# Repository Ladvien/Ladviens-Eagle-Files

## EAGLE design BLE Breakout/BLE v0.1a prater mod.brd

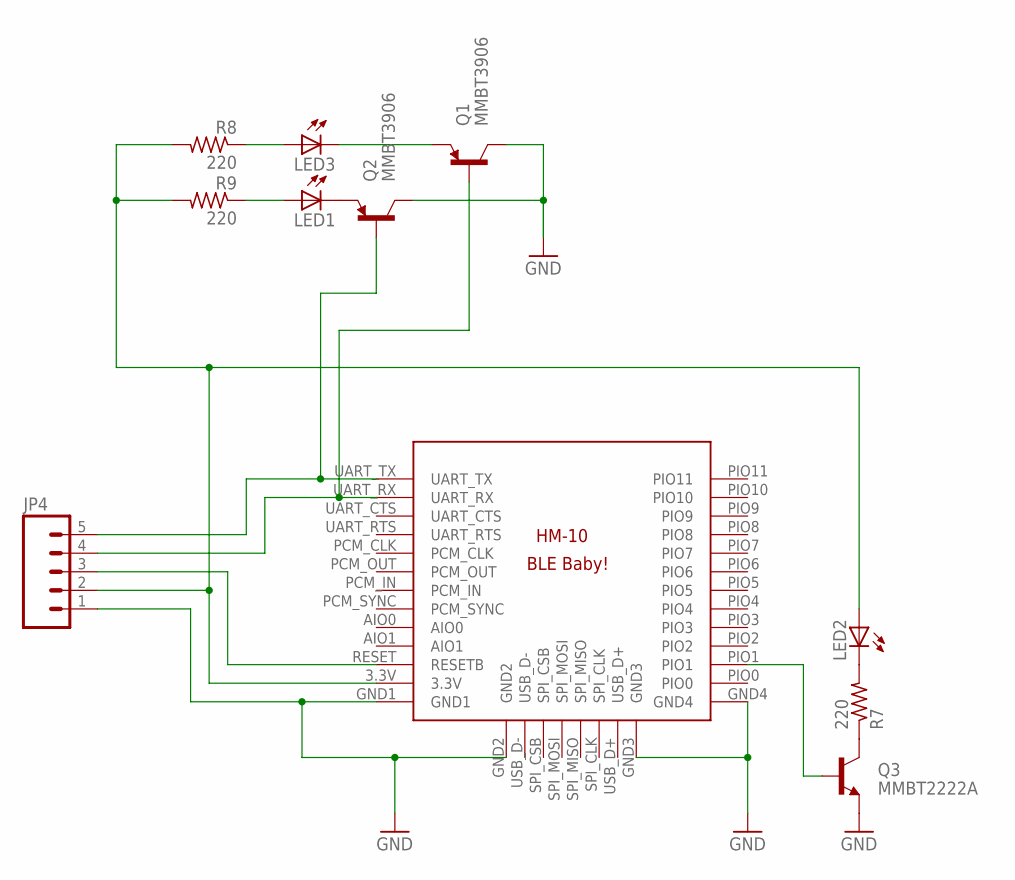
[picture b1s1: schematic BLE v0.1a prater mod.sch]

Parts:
JP4: M05PTH; 1X05
LED1, LED2, LED3: LED0603; LED-0603
Q1, Q2: MMBT3906; SOT23
Q3: MMBT2222A; SOT23
R7, R8, R9: 220; M0805
U$1: BLE-HM-10

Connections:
GND: JP4.1, Q1.3 (C), Q2.3 (C), Q3.2 (E), U$1.GND1, U$1.GND2, U$1.GND3, U$1.GND4
HVTX->LVRX: JP4.4, Q1.1 (B), U$1.UART_RX
LVRX->HVTX: JP4.5, Q2.1 (B), U$1.UART_TX
unnamed: Q3.3 (C), R7.1
unnamed: JP4.2, LED2.A, R8.2, R9.2, U$1.3.3V
unnamed: JP4.3, U$1.RESET (RESETB)
unnamed: Q3.1 (B), U$1.PIO1
unnamed: LED2.C, R7.2
unnamed: LED3.C, Q1.2 (E)
unnamed: LED1.A, R9.1
unnamed: LED3.A, R8.1
unnamed: LED1.C, Q2.2 (E)

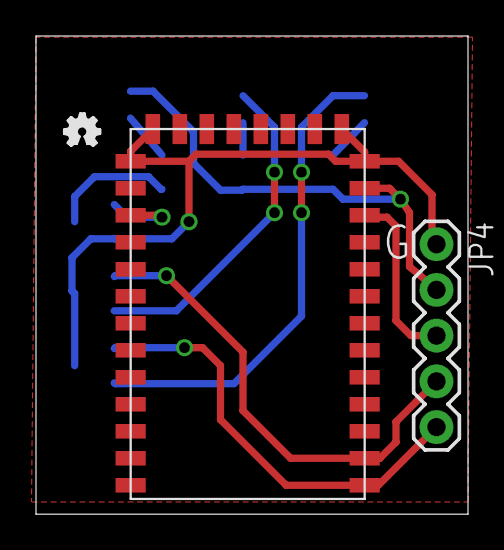
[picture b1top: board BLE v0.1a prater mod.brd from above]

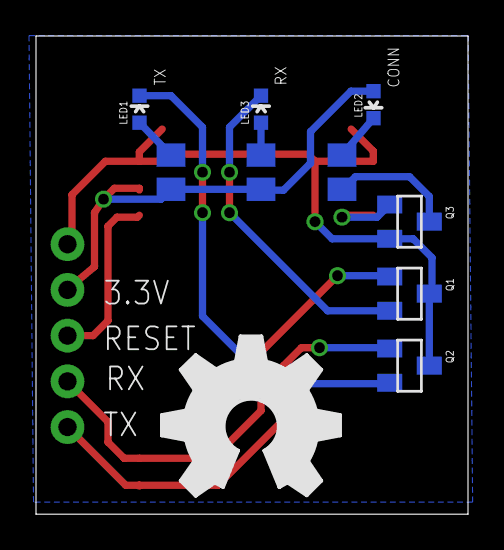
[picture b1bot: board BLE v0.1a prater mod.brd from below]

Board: 2 copper layers, 24.0 x 26.6 mm, 13 parts (10 on the bottom side), 12 nets.

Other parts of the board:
U$2: OSHW_FILLX350_NOTEXT
U$3: OSHW_FILLX70_NOTEXT

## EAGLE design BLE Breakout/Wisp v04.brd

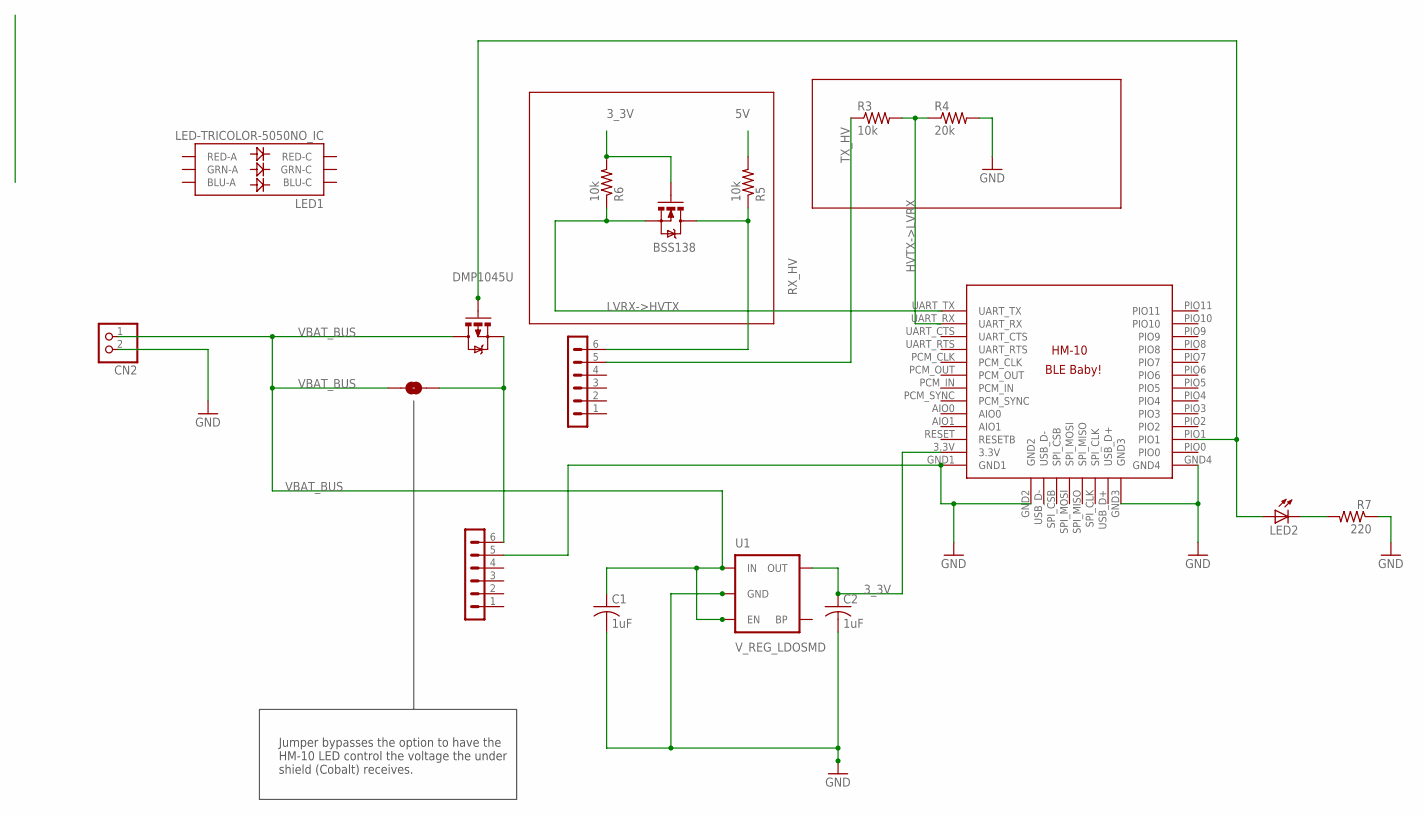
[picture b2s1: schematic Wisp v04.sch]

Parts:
BSS138: MOSFET-NCHANNELSMD; SOT23-3
C1, C2: 1uF; C0805K
CN2: JST_2PIN-THM; JST-PH-2-THM
DMP1045U: MOSFET-PCHANNELSMD; SOT23-3
LED1: LED-TRICOLOR-5050NO_IC; LED-TRICOLOR-5050
LED2: LED0603; LED-0603
R3, R5, R6: 10k; R0402
R4: 20k; R0402
R7: 220; R0402
SJ2: SOLDERJUMPERNO; SJ_2S-NO
U1: V_REG_LDOSMD; SOT23-5
U$1: BLE-HM-10
U$4, U$5: 1X6_SHORT_ROUND

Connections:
3_3V: BSS138.1 (G), C2.1, R6.2, U1.5 (OUT), U$1.3.3V
5V: R5.2
GND: C1.2, C2.2, CN2.2 (1), R4.2, R7.1, U1.2 (GND), U$1.GND1, U$1.GND2, U$1.GND3, U$1.GND4, U$5.5
HVTX->LVRX: R3.2, R4.1, U$1.UART_RX
LVRX->HVTX: BSS138.2 (S), R6.1, U$1.UART_TX
unnamed: DMP1045U.2 (S), SJ2.1, U$5.6
unnamed: DMP1045U.1 (G), LED2.A, U$1.PIO1
unnamed: LED2.C, R7.2
RX_HV: BSS138.3 (D), R5.1, U$4.6
TX_HV: R3.1, U$4.5
VBAT_BUS: C1.1, CN2.1 (2), DMP1045U.3 (D), SJ2.2, U1.1 (IN), U1.3 (EN)

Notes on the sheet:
Jumper bypasses the option to have the HM-10 LED control the voltage the under shield (Cobalt) receives.

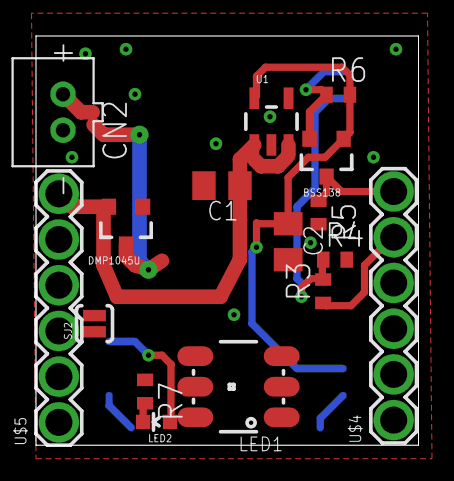
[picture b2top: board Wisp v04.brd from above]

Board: 2 copper layers, 21.2 x 22.7 mm, 17 parts (1 on the bottom side), 10 nets.

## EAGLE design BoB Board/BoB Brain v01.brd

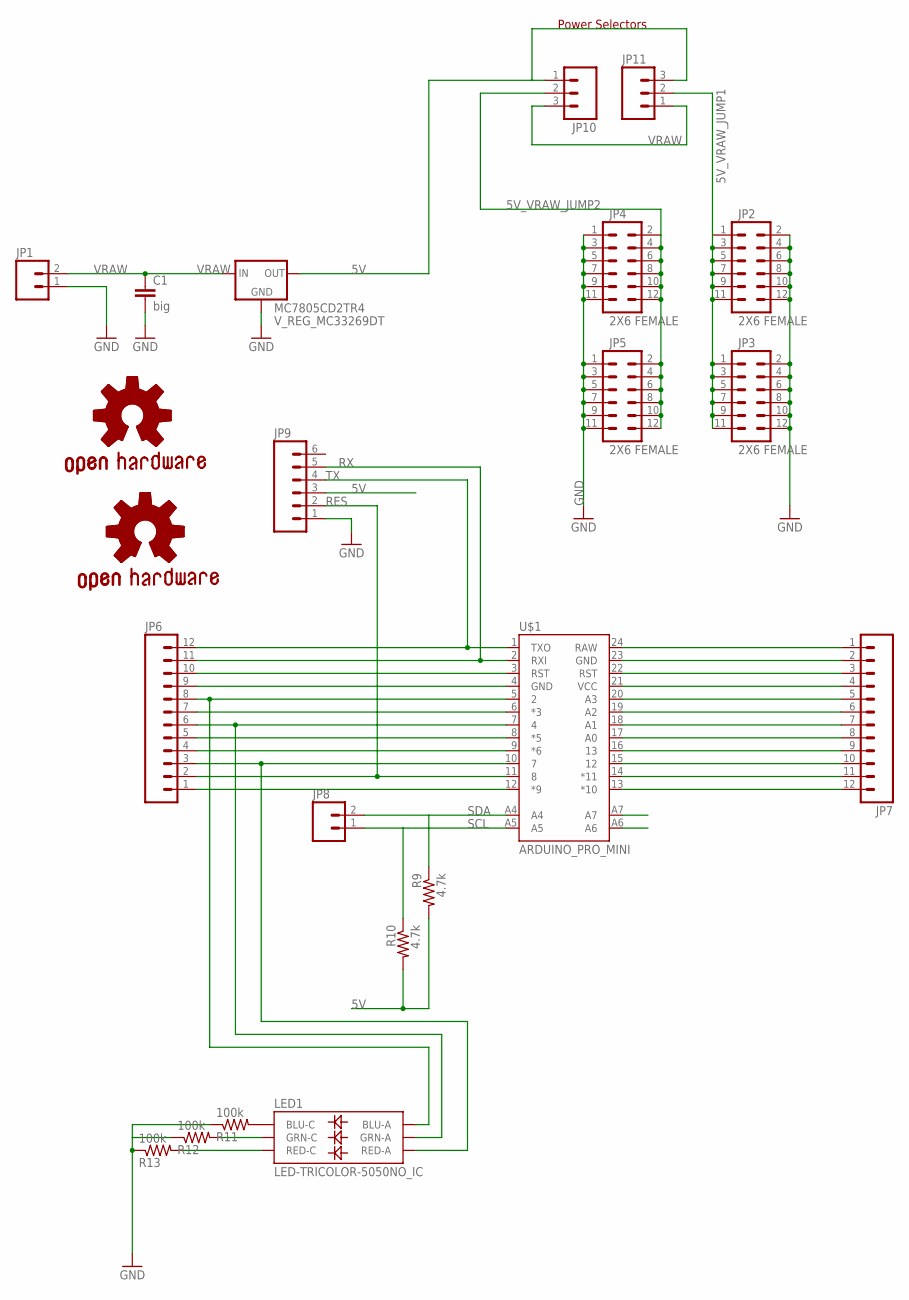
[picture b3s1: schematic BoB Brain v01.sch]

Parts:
C1: big; CAP-PTH-5MM
GOLD_ORB_SM1: OSHWLOGO_GOLD_ORB_MED; OSHW1
GOLD_ORB_SM2: OSHWLOGO_GOLD_ORB_SM; OSHW2
JP1: M025MM; SCREWTERMINAL-5MM-2
JP2, JP3, JP4, JP5: 2X6 FEMALE; 2X6
JP6, JP7: M12PTH; 1X12
JP8: M02LOCK; 1X02_LOCK
JP9: M06LOCK; 1X06_LOCK
JP10, JP11: M03PTH; 1X03
LED1: LED-TRICOLOR-5050NO_IC; LED-TRICOLOR-5050
MC7805CD2TR4: V_REG_MC33269DT; DPAK
R9, R10: 4.7k; M0805
R11, R12, R13: 100k; R0805W
U$1: ARDUINO_PRO_MINI

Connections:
5V: JP9.3, JP10.1, JP11.3, MC7805CD2TR4.4 (OUT), R9.2, R10.2
5V_VRAW_JUMP1: JP2.1, JP2.3, JP2.5, JP2.7, JP2.9, JP2.11, JP3.1, JP3.3, JP3.5, JP3.7, JP3.9, JP3.11, JP11.2
5V_VRAW_JUMP2: JP4.2, JP4.4, JP4.6, JP4.8, JP4.10, JP4.12, JP5.2, JP5.4, JP5.6, JP5.8, JP5.10, JP5.12, JP10.2
APM_PIN_3: JP6.7, U$1.6 (*3)
APM_PIN_5: JP6.5, U$1.8 (*5)
APM_PIN_6: JP6.4, U$1.9 (*6)
APM_PIN_9: JP6.1, U$1.12 (*9)
GND: C1.2, JP1.1, JP2.2, JP2.4, JP2.6, JP2.8, JP2.10, JP2.12, JP3.2, JP3.4, JP3.6, JP3.8, JP3.10, JP3.12, JP4.1, JP4.3, JP4.5, JP4.7, JP4.9, JP4.11, JP5.1, JP5.3, JP5.5, JP5.7, JP5.9, JP5.11, JP9.1, MC7805CD2TR4.1 (GND), R11.1, R12.1, R13.1
unnamed: JP6.10, U$1.3 (RST)
unnamed: JP6.9, U$1.4 (GND)
unnamed: JP6.8, LED1.3 (BLU-A), U$1.5 (2)
unnamed: LED1.4 (BLU-C), R11.2
unnamed: JP6.6, LED1.1 (GRN-A), U$1.7 (4)
unnamed: LED1.6 (GRN-C), R12.2
unnamed: LED1.5 (RED-C), R13.2
unnamed: JP6.3, LED1.2 (RED-A), U$1.10 (7)
unnamed: JP7.1, U$1.24 (RAW)
unnamed: JP7.2, U$1.23 (GND)
unnamed: JP7.3, U$1.22 (RST)
unnamed: JP7.4, U$1.21 (VCC)
unnamed: JP7.5, U$1.20 (A3)
unnamed: JP7.6, U$1.19 (A2)
unnamed: JP7.7, U$1.18 (A1)
unnamed: JP7.8, U$1.17 (A0)
unnamed: JP7.9, U$1.16 (13)
unnamed: JP7.10, U$1.15 (12)
unnamed: JP7.11, U$1.14 (*11)
unnamed: JP7.12, U$1.13 (*10)
RES: JP6.2, JP9.2, U$1.11 (8)
RX: JP6.11, JP9.5, U$1.2 (RXI)
SCL: JP8.1, R10.1, U$1.A5
SDA: JP8.2, R9.1, U$1.A4
TX: JP6.12, JP9.4, U$1.1 (TXO)
VRAW: C1.1, JP1.2, JP10.3, JP11.1, MC7805CD2TR4.3 (IN)

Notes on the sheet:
Power Selectors

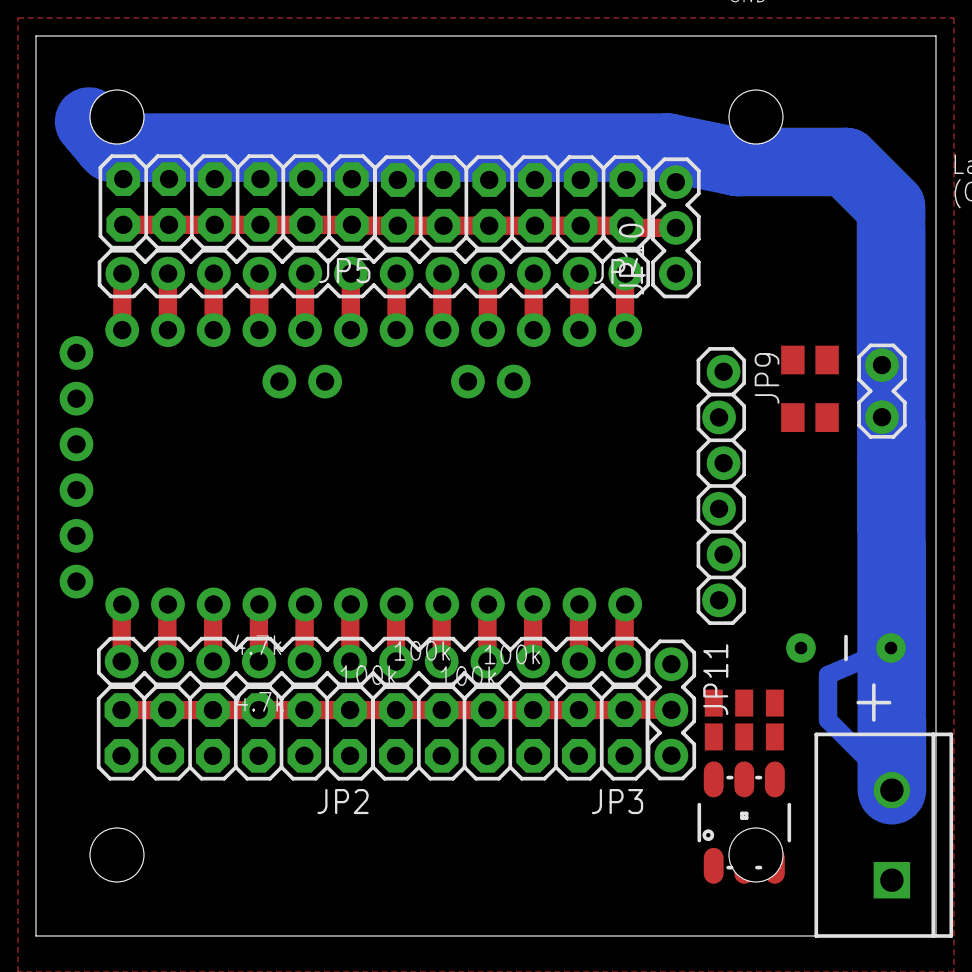
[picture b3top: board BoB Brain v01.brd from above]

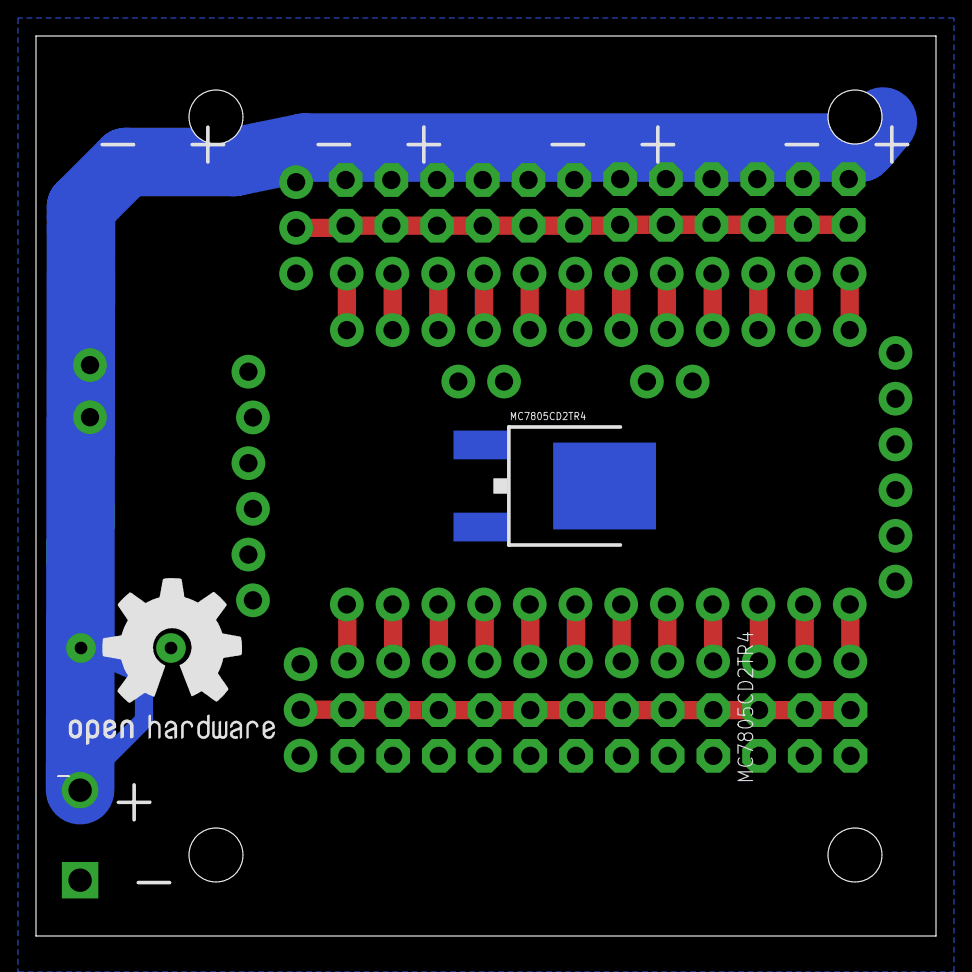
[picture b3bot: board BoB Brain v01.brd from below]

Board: 2 copper layers, 50.0 x 50.0 mm, 22 parts (2 on the bottom side), 34 nets.

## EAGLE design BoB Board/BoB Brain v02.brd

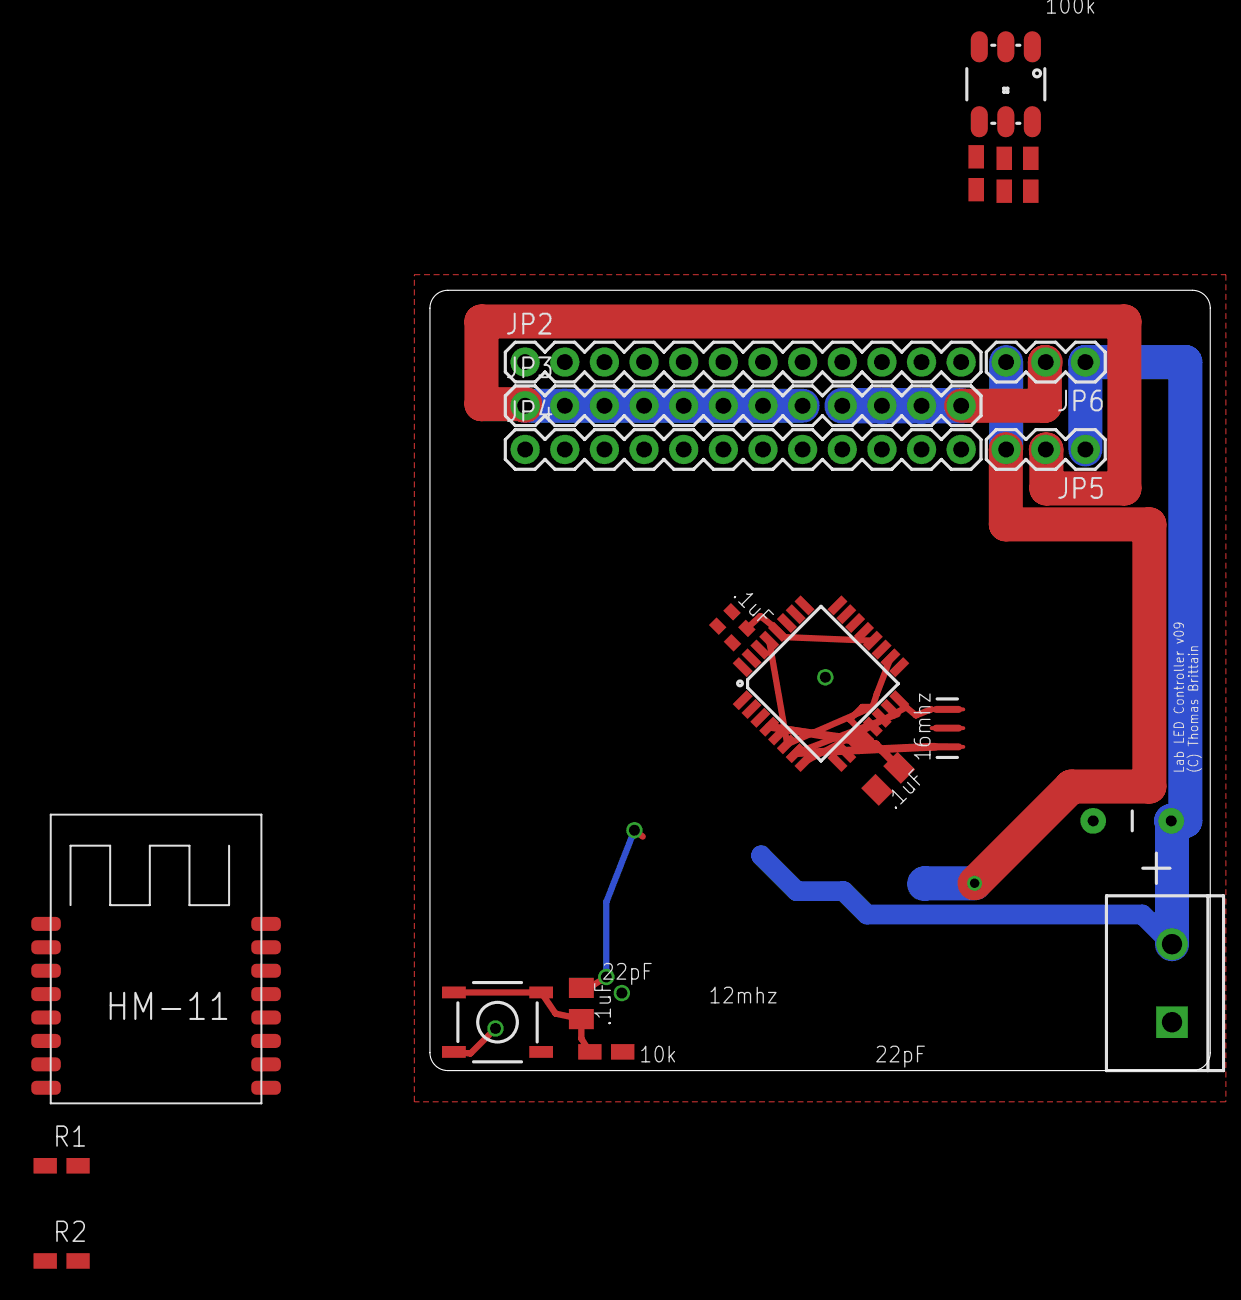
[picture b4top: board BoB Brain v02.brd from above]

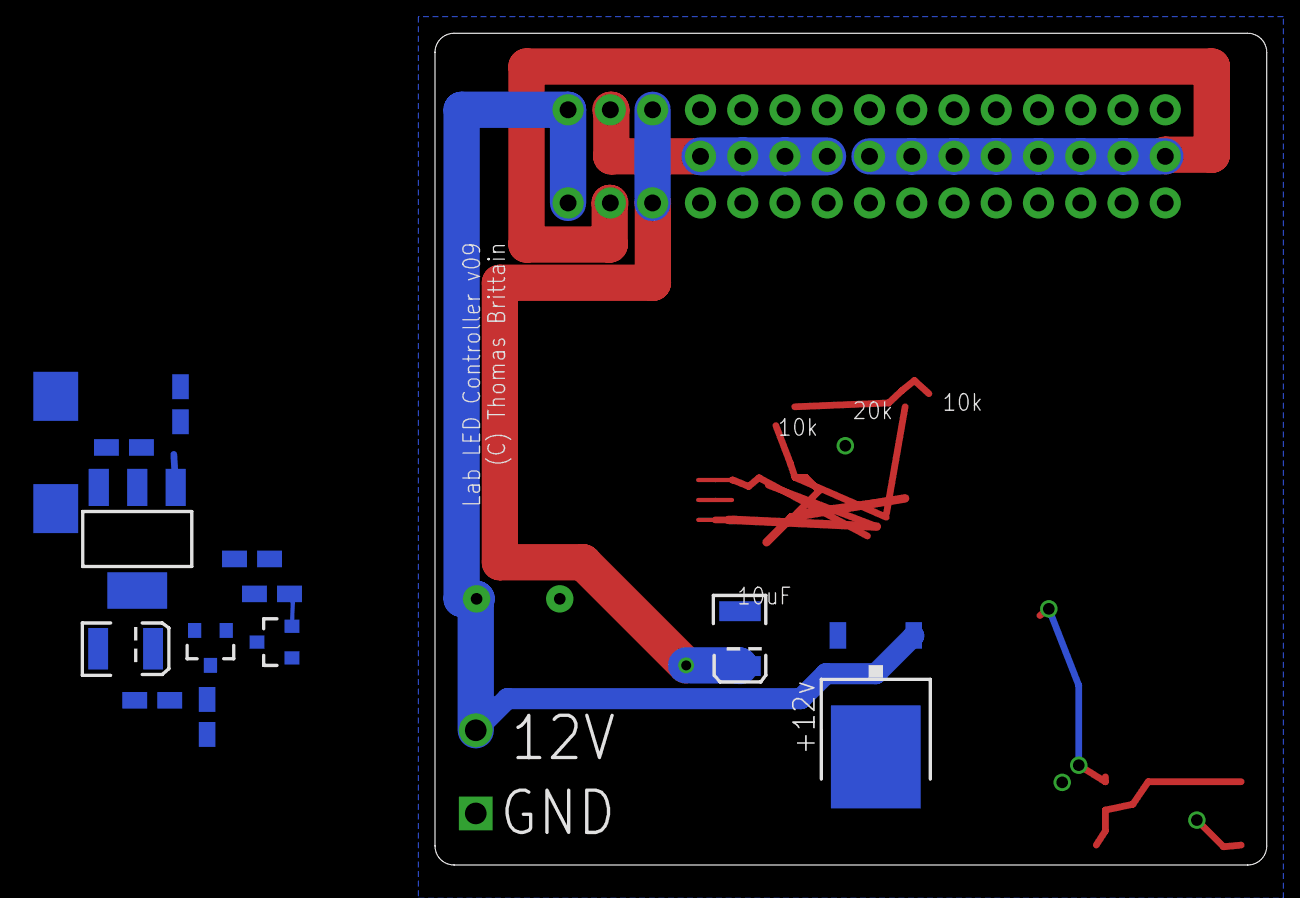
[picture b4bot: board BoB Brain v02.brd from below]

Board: 2 copper layers, 50.0 x 50.0 mm, 35 parts (13 on the bottom side), 23 nets.

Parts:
C1: big; CAP-PTH-5MM
C2, C10: 10uF; EIA3528
C3, C8: 0.1uF; C0402
C4, C5: 0.1uF; C0805K
C11: 470uF; D/7343-31W
JP1: 12V_INPUT; SCREWTERMINAL-5MM-2
JP2, JP3, JP4: 1X12
JP5, JP6: JUMPER-3PTH; 1X03
LED1: LED-TRICOLOR-5050NO_IC; LED-TRICOLOR-5050
Q1, Q9: MOSFET-NCHANNELAO3404A; SOT23-3
R1, R2: 1K; R0805W
R11, R12, R13: 100k; R0805W
R14, R19, R20, R21, R22: 10k; R0805W
R17: 220; R0805W
R18: 370; R0805W
S1: TAC_SWITCHSMD; TACTILE-SWITCH-SMD
U1: ATMEGA328P_TQFP; TQFP32-08
U3: +12v; TO-252
U4: V_REG_317SMD; SOT223
U$1: HM-11
Y1: 16MHZ; RESONATOR-SMD

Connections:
3.35V: C11.+, Q1.1, Q9.1, R17.2, R21.2, R22.2, U4.2, U$1.9
6V: JP3.9, JP3.10, JP3.11, JP3.12, JP6.2
13: LED1.2, U1.17
A1: LED1.1, U1.24
A2: LED1.3, U1.25
ATMEGA-RESET: R2.1, U$1.14
GND: C1.2, C2.C, C3.2, C4.2, C8.2, C10.C, C11.-, JP1.1, JP2.1, JP2.2, JP2.3, JP2.4, JP2.5, JP2.6, JP2.7, JP2.8, JP2.9, JP2.10, JP2.11, JP2.12, R11.1, R12.1, R13.1, R18.1, S1.1, S1.2, U1.3, U1.5, U1.21, U3.3, U$1.12, Y1.2
HM-RESET: R1.1, U1.32
unnamed: C3.1, U1.20
unnamed: U1.7, Y1.1
unnamed: LED1.4, R11.2
unnamed: LED1.6, R12.2
unnamed: LED1.5, R13.2
unnamed: U1.8, Y1.3
unnamed: Q1.2, R22.1, U$1.2
unnamed: R17.1, R18.2, U4.1
unnamed: Q9.2, R21.1, U$1.4
PIN_PWR: JP3.1, JP3.2, JP3.3, JP3.4, JP3.5, JP3.6, JP3.7, JP3.8, JP5.2
RAW: C1.1, JP1.2, JP5.1, JP6.1, U3.1
RESET: C5.2, R1.2, R2.2, R14.1, S1.3, S1.4, U1.29, U$1.11
U2_RX: Q1.3, R20.1, U1.31
U2_TX: Q9.3, R19.1, U1.30
VCC: C2.A, C4.1, C8.1, C10.A, JP5.3, JP6.3, R14.2, R19.2, R20.2, U1.4, U1.6, U1.18, U3.2, U4.3

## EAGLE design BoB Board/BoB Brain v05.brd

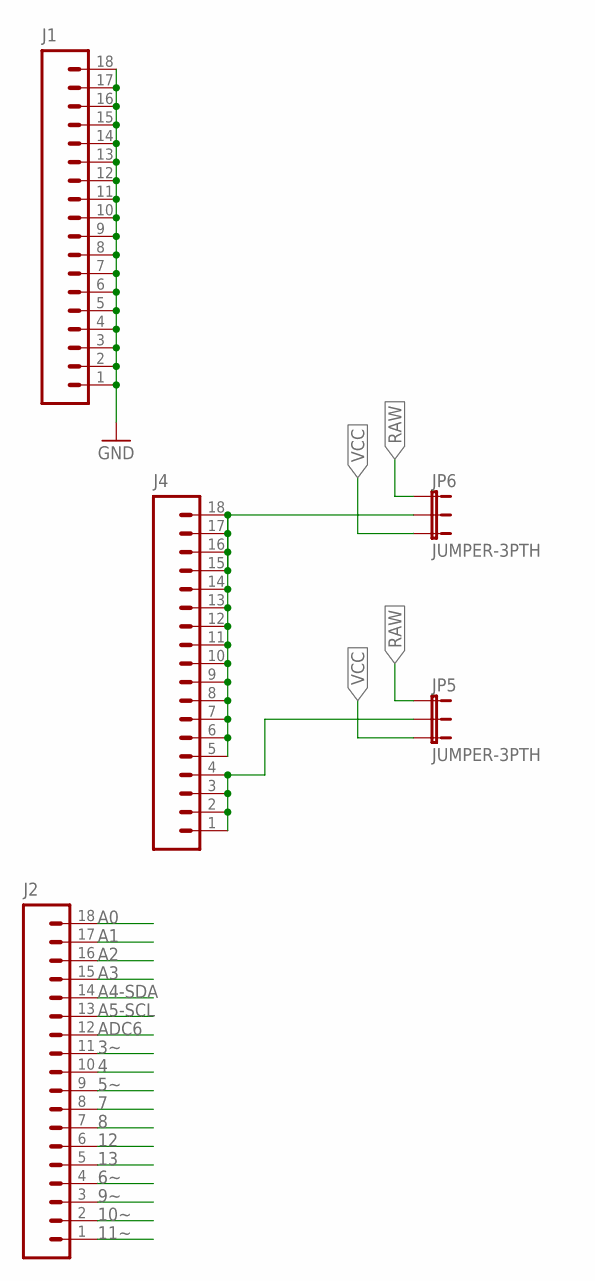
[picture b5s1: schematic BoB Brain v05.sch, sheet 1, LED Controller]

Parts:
J1, J2, J4: M18_; 1X18
JP5, JP6: JUMPER-3PTH; 1X03

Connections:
3~: J2.18; also elsewhere on the board
4: J2.17; also elsewhere on the board
5~: J2.9; also elsewhere on the board
6V: J4.5, J4.6, J4.7, J4.8, J4.9, J4.10, J4.11, J4.12, J4.13, J4.14, J4.15, J4.16, J4.17, J4.18, JP6.2
6~: J2.4; also elsewhere on the board
7: J2.8; also elsewhere on the board
8: J2.7; also elsewhere on the board
9~: J2.3; also elsewhere on the board
10~: J2.2; also elsewhere on the board
11~: J2.1; also elsewhere on the board
12: J2.6; also elsewhere on the board
13: J2.5; also elsewhere on the board
A0: J2.12; also elsewhere on the board
A1: J2.10; also elsewhere on the board
A2: J2.16; also elsewhere on the board
A3: J2.13; also elsewhere on the board
A4-SDA: J2.14; also elsewhere on the board
A5-SCL: J2.15; also elsewhere on the board
ADC6: J2.11; also elsewhere on the board
GND: J1.1, J1.2, J1.3, J1.4, J1.5, J1.6, J1.7, J1.8, J1.9, J1.10, J1.11, J1.12, J1.13, J1.14, J1.15, J1.16, J1.17, J1.18; also elsewhere on the board
PIN_PWR: J4.1, J4.2, J4.3, J4.4, JP5.2
RAW: JP5.1, JP6.1; also elsewhere on the board
VCC: JP5.3, JP6.3; also elsewhere on the board

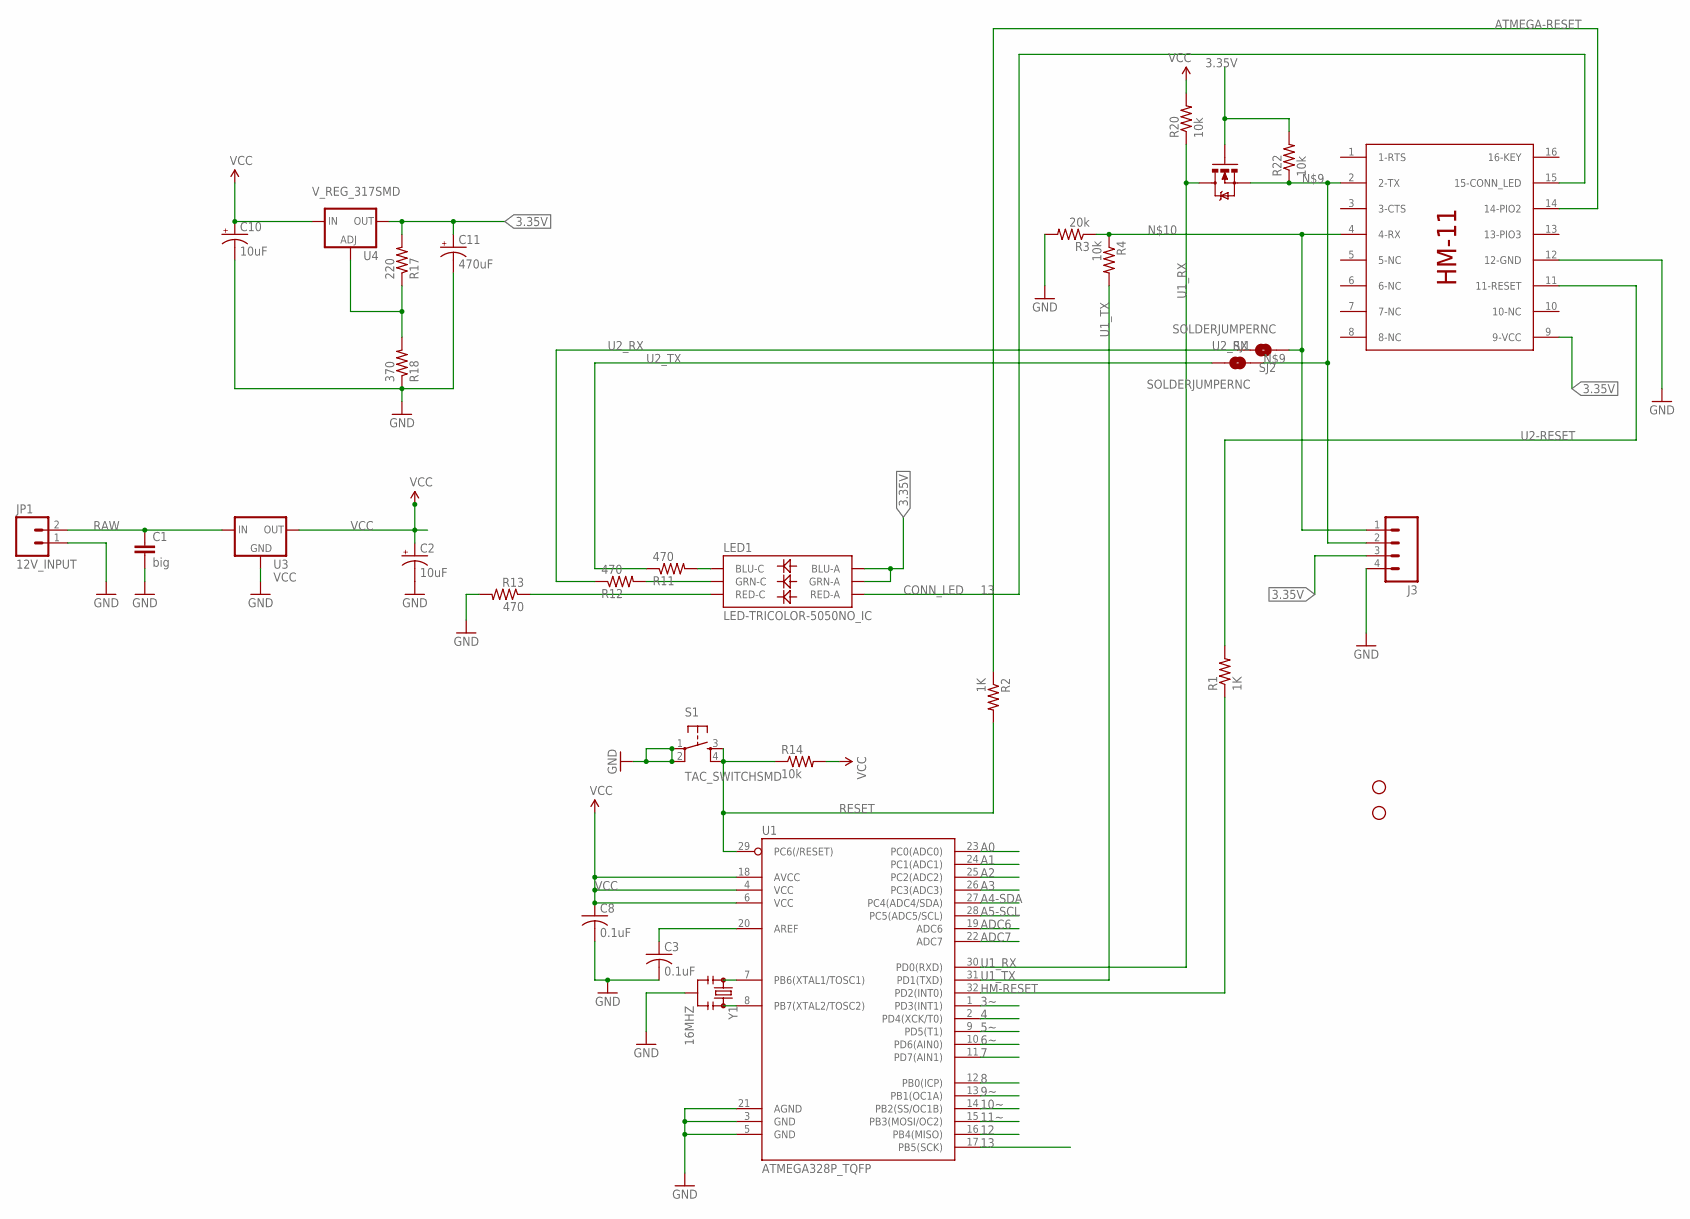
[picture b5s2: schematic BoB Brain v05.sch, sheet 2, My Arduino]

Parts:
C1: big; CAP-PTH-5MM
C2, C10: 10uF; EIA3528
C3, C8: 0.1uF; C0402
C11: 470uF; CT3528
H1, H2: STAND-OFF
J3: M04PTH; 1X04
JP1: 12V_INPUT; SCREWTERMINAL-5MM-2
LED1: LED-TRICOLOR-5050NO_IC; LED-TRICOLOR-5050
Q1: MOSFET-NCHANNELAO3404A; SOT23-3
R1, R2: 1K; R0805W
R3: 20k; R0805W
R4, R14, R20, R22: 10k; R0805W
R11, R12, R13: 470; R0805W
R17: 220; R0805W
R18: 370; R0805W
S1: TAC_SWITCHSMD; TACTILE-SWITCH-SMD
SJ1, SJ2: SOLDERJUMPERNC; SJ_2S
U1: ATMEGA328P_TQFP; TQFP32-08
U3: VCC; TO-252
U4: V_REG_317SMD; SOT223
U$1: HM-11
Y1: 16MHZ; RESONATOR-SMD

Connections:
3.35V: C11.- (+), J3.3, LED1.1 (GRN-A), LED1.3 (BLU-A), Q1.1 (G), R17.2, R22.2, U4.2 (OUT), U$1.9 (9-VCC)
3~: U1.1 (PD3(INT1)); also elsewhere on the board
4: U1.2 (PD4(XCK/T0)); also elsewhere on the board
5~: U1.9 (PD5(T1)); also elsewhere on the board
6~: U1.10 (PD6(AIN0)); also elsewhere on the board
7: U1.11 (PD7(AIN1)); also elsewhere on the board
8: U1.12 (PB0(ICP)); also elsewhere on the board
9~: U1.13 (PB1(OC1A)); also elsewhere on the board
10~: U1.14 (PB2(SS/OC1B)); also elsewhere on the board
11~: U1.15 (PB3(MOSI/OC2)); also elsewhere on the board
12: U1.16 (PB4(MISO)); also elsewhere on the board
13: U1.17 (PB5(SCK)); also elsewhere on the board
A0: U1.23 (PC0(ADC0)); also elsewhere on the board
A1: U1.24 (PC1(ADC1)); also elsewhere on the board
A2: U1.25 (PC2(ADC2)); also elsewhere on the board
A3: U1.26 (PC3(ADC3)); also elsewhere on the board
A4-SDA: U1.27 (PC4(ADC4/SDA)); also elsewhere on the board
A5-SCL: U1.28 (PC5(ADC5/SCL)); also elsewhere on the board
ADC6: U1.19 (ADC6); also elsewhere on the board
ADC7: U1.22 (ADC7)
AREF: C3.1, U1.20 (AREF)
ATMEGA-RESET: R2.1, U$1.14 (14-PIO2)
CONN_LED: LED1.2 (RED-A), U$1.15 (15-CONN_LED)
GND: C1.2, C2.C (-), C3.2, C8.2, C10.C (-), C11.+ (-), J3.4, JP1.1, R3.2, R13.2, R18.1, S1.1, S1.2, U1.3 (GND), U1.5 (GND), U1.21 (AGND), U3.3 (GND), U$1.12 (12-GND), Y1.2; also elsewhere on the board
HM-RESET: R1.1, U1.32 (PD2(INT0))
unnamed: LED1.5 (RED-C), R13.1
unnamed: U1.7 (PB6(XTAL1/TOSC1)), Y1.1
unnamed: LED1.4 (BLU-C), R11.2
unnamed: LED1.6 (GRN-C), R12.2
unnamed: J3.2, Q1.2 (S), R22.1, SJ1.1, U$1.2 (2-TX)
unnamed: J3.1, R3.1, R4.1, SJ2.1, U$1.4 (4-RX)
unnamed: U1.8 (PB7(XTAL2/TOSC2)), Y1.3
unnamed: R17.1, R18.2, U4.1 (ADJ)
RAW: C1.1, JP1.2, U3.1 (IN); also elsewhere on the board
RESET: R2.2, R14.1, S1.3, S1.4, U1.29 (PC6(/RESET))
U1_RX: Q1.3 (D), R20.1, U1.30 (PD0(RXD))
U1_TX: R4.2, U1.31 (PD1(TXD))
U2-RESET: R1.2, U$1.11 (11-RESET)
U2_RX: R12.1, SJ2.2
U2_TX: R11.1, SJ1.2
VCC: C2.A (+), C8.1, C10.A (+), R14.2, R20.2, U1.4 (VCC), U1.6 (VCC), U1.18 (AVCC), U3.2 (OUT), U4.3 (IN); also elsewhere on the board

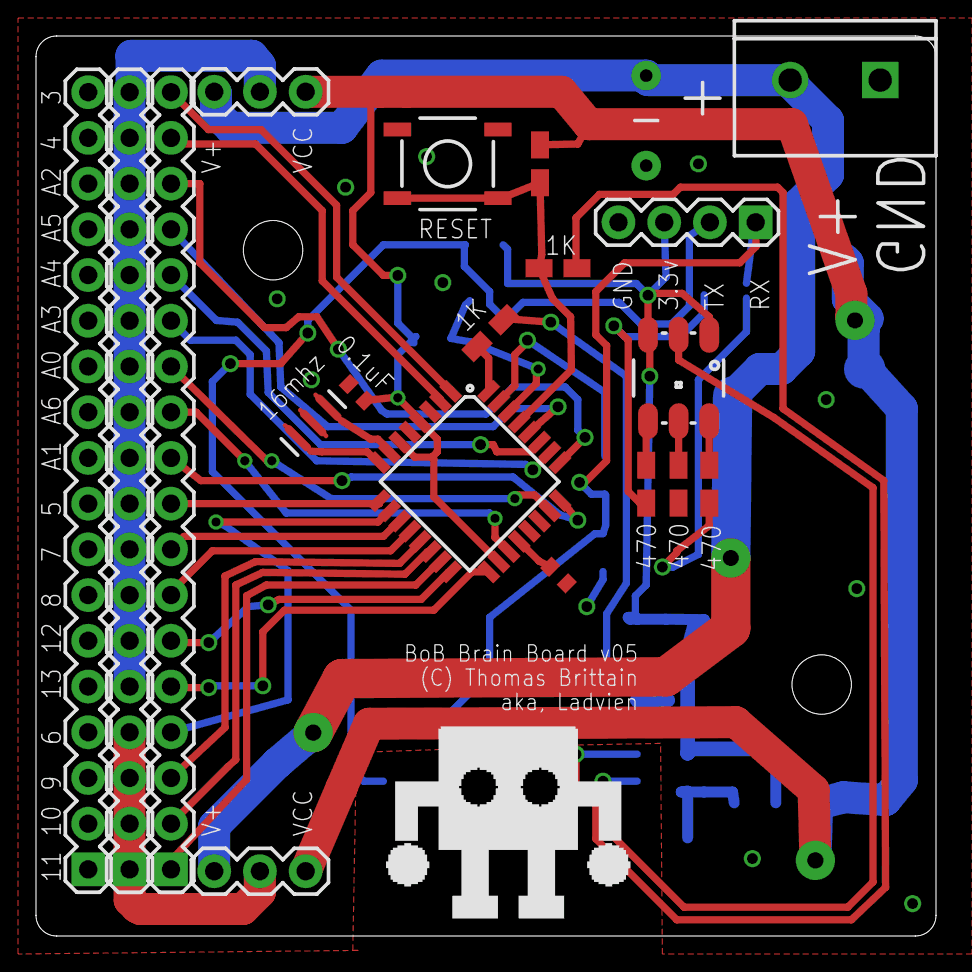
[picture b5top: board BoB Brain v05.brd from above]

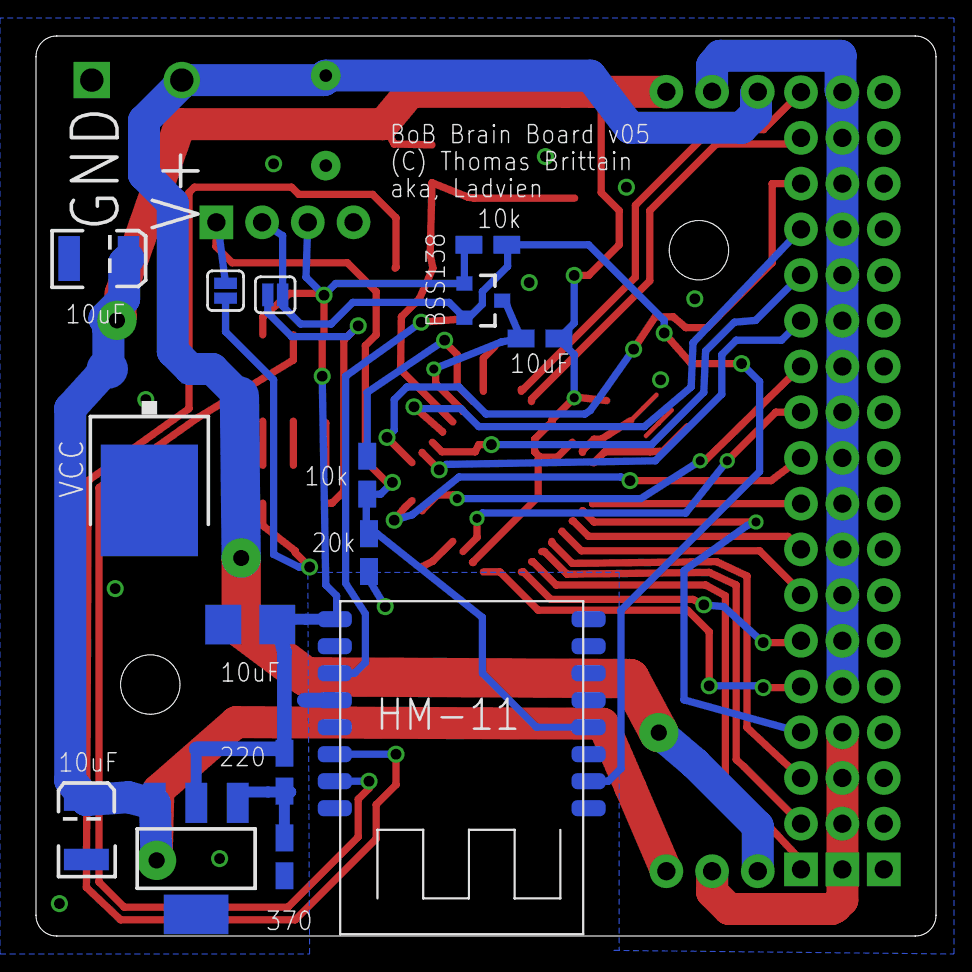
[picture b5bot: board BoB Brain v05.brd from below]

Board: 2 copper layers, 50.0 x 50.0 mm, 37 parts (15 on the bottom side), 42 nets.

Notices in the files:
parts and their libraries:
SparkFun: Licensing: CC v3.0 Share-Alike You are welcome to use this library for commercial purposes.
SparkFun-Boards: Licensing: Creative Commons ShareAlike 4.0 International - https://creativecommons.org/licenses/by-sa/4.0
